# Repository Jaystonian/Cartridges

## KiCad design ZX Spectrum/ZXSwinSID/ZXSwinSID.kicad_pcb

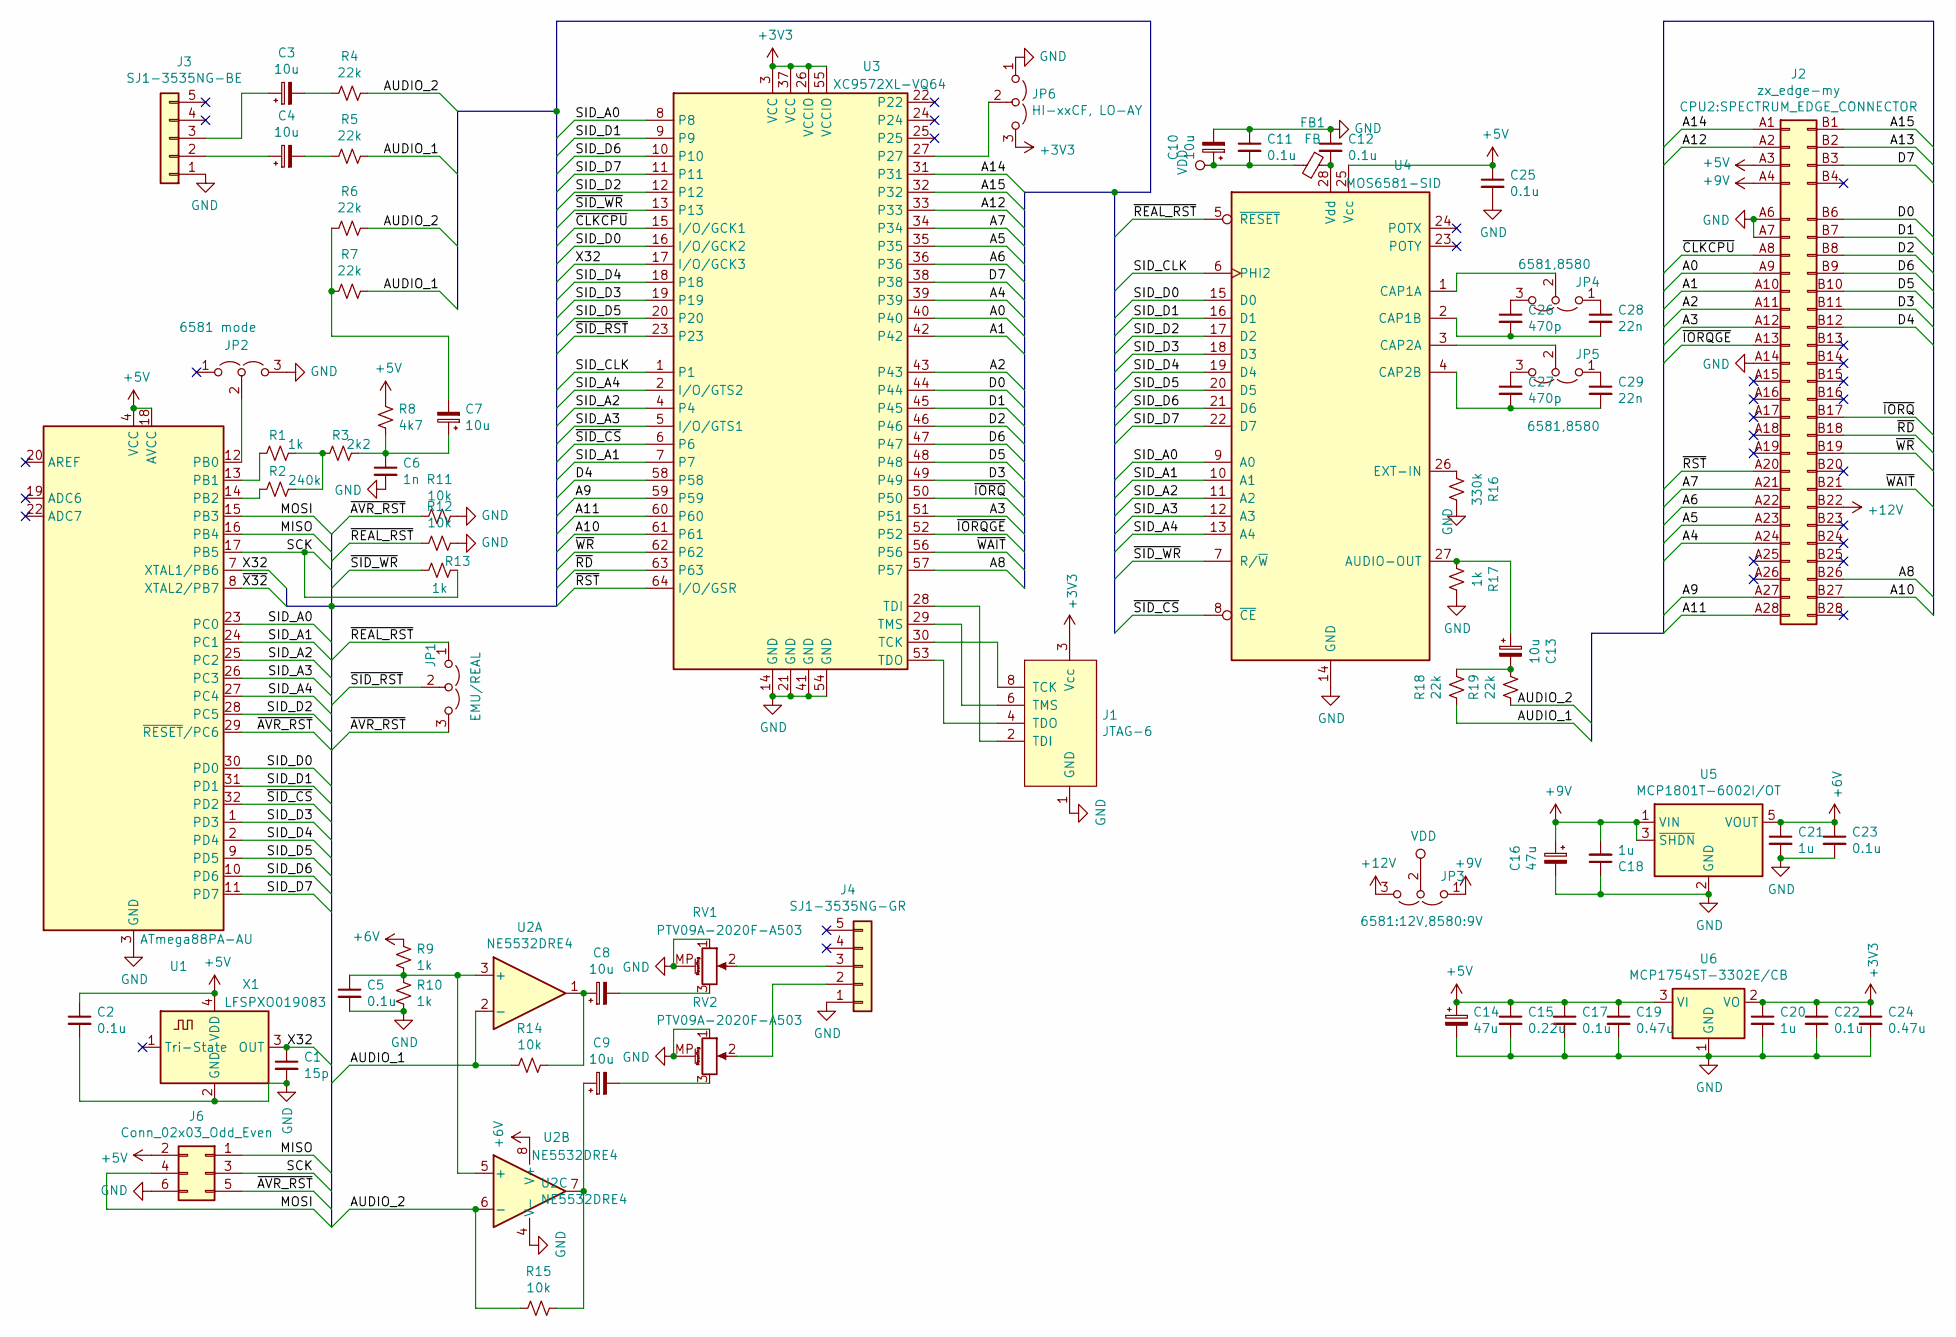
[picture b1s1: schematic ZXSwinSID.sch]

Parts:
C1: 15p; C_0805_2012Metric_Pad1.15x1.40mm_HandSolder
C2, C5, C11, C12, C17, C22, C23, C25: 0.1u; C_0805_2012Metric_Pad1.15x1.40mm_HandSolder
C3, C4, C7, C8, C9, C10, C13: 10u; CP_EIA-3216-18_Kemet-A_Pad1.58x1.35mm_HandSolder
C6: 1n; C_0805_2012Metric_Pad1.15x1.40mm_HandSolder
C14, C16: 47u; CP_EIA-6032-28_Kemet-C_Pad2.25x2.35mm_HandSolder
C15: 0.22u; C_0805_2012Metric_Pad1.15x1.40mm_HandSolder
C18, C20, C21: 1u; C_0805_2012Metric_Pad1.15x1.40mm_HandSolder
C19, C24: 0.47u; C_0805_2012Metric_Pad1.15x1.40mm_HandSolder
C26, C27: 470p; C_0805_2012Metric_Pad1.15x1.40mm_HandSolder
C28, C29: 22n; C_0805_2012Metric_Pad1.15x1.40mm_HandSolder
FB1: FB; R_0805_2012Metric_Pad1.15x1.40mm_HandSolder
J1: JTAG-6
J2: zx_edge-my; SPECTRUM_EDGE_CONNECTOR
J3: SJ1-3535NG-BE; Audio_SJ1-3535NG
J4: SJ1-3535NG-GR; Audio_SJ1-3535NG
J6: Conn_02x03_Odd_Even; PinHeader_1x06_P2.54mm_Vertical_SMD_Pin1Right
JP1: EMU/REAL; PinHeader_1x03_P2.54mm_Vertical
JP2: 6581 mode; PinHeader_1x03_P2.54mm_Vertical
JP3: 6581:12V,8580:9V; PinHeader_1x03_P2.54mm_Vertical
JP4, JP5: 6581,8580; PinHeader_1x03_P2.54mm_Vertical
JP6: HI-xxCF, LO-AY; PinHeader_1x03_P2.54mm_Vertical
R1, R9, R10, R13, R17: 1k; R_0805_2012Metric_Pad1.15x1.40mm_HandSolder
R2: 240k; R_0805_2012Metric_Pad1.15x1.40mm_HandSolder
R3: 2k2; R_0805_2012Metric_Pad1.15x1.40mm_HandSolder
R4, R5, R6, R7, R18, R19: 22k; R_0805_2012Metric_Pad1.15x1.40mm_HandSolder
R8: 4k7; R_0805_2012Metric_Pad1.15x1.40mm_HandSolder
R11, R12, R14, R15: 10k; R_0805_2012Metric_Pad1.15x1.40mm_HandSolder
R16: 330k; R_0805_2012Metric_Pad1.15x1.40mm_HandSolder
RV1, RV2: PTV09A-2020F-A503; Potentiometer_Bourns_PTV09A-2_Single_Horizontal
U1: ATmega88PA-AU; TQFP-32_7x7mm_P0.8mm
U2: NE5532DRE4; SOIC-8_3.9x4.9mm_P1.27mm
U3: XC9572XL-VQ64; TQFP-64_10x10mm_P0.5mm
U4: MOS6581-SID; DIP-28_W15.24mm_Socket
U5: MCP1801T-6002I/OT; SOT-23-5
U6: MCP1754ST-3302E/CB; SOT-23
X1: LFSPXO019083; Oscillator_SMD_IQD_IQXO70-4Pin_7.5x5.0mm_HandSoldering

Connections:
+3V3: C20.1, C22.1, C24.1, J1.3 (Vcc), JP6.3 (B), U3.3 (VCC), U3.26 (VCCIO), U3.37 (VCC), U3.55 (VCCIO), U6.2 (VO)
+5V: C2.1, C14.1, C15.1, C17.1, C19.1, C25.1, J2.A3 (Pin_a3), J6.2, R8.2, U1.4 (VCC), U1.6 (VCC), U1.18 (AVCC), U4.25 (Vcc), U6.3 (VI), X1.4 (VDD)
+6V: C21.1, C23.1, R9.1, U2.8 (V+), U5.5 (VOUT)
+9V: C16.1, C18.2, J2.A4 (Pin_a4), JP3.1 (A), U5.1 (VIN), U5.3 (~SHDN)
+12V: J2.B22 (Pin_b22), JP3.3 (B)
/A0: J2.A9 (Pin_a9), U3.40
/A1: J2.A10 (Pin_a10), U3.42
/A2: J2.A11 (Pin_a11), U3.43
/A3: J2.A12 (Pin_a12), U3.51
/A4: J2.A24 (Pin_a24), U3.39
/A5: J2.A23 (Pin_a23), U3.35
/A6: J2.A22 (Pin_a22), U3.36
/A7: J2.A21 (Pin_a21), U3.34
/A8: J2.B26 (Pin_b26), U3.57
/A9: J2.A27 (Pin_a27), U3.59
/A10: J2.B27 (Pin_b27), U3.61
/A11: J2.A28 (Pin_a28), U3.60
/A12: J2.A2 (Pin_a2), U3.33
/A13: J2.B2 (Pin_b2)
/A14: J2.A1 (Pin_a1), U3.31
/A15: J2.B1 (Pin_b1), U3.32
/AUDIO_1: R5.1, R7.1, R14.2, R18.2, U2.2 (-)
/AUDIO_2: R4.1, R6.1, R15.2, R19.2, U2.6 (-)
/D0: J2.B6 (Pin_b6), U3.44
/D1: J2.B7 (Pin_b7), U3.45
/D2: J2.B8 (Pin_b8), U3.46
/D3: J2.B11 (Pin_b11), U3.49
/D4: J2.B12 (Pin_b12), U3.58
/D5: J2.B10 (Pin_b10), U3.48
/D6: J2.B9 (Pin_b9), U3.47
/D7: J2.B3 (Pin_b3), U3.38
/MISO: J6.1, U1.16 (PB4)
/MOSI: J6.4, U1.15 (PB3)
/SCK: J6.3, R13.1, U1.17 (PB5)
/SID_A0: U1.23 (PC0), U3.8, U4.9 (A0)
/SID_A1: U1.24 (PC1), U3.7, U4.10 (A1)
/SID_A2: U1.25 (PC2), U3.4, U4.11 (A2)
/SID_A3: U1.26 (PC3), U3.5 (I/O/GTS1), U4.12 (A3)
/SID_A4: U1.27 (PC4), U3.2 (I/O/GTS2), U4.13 (A4)
/SID_CLK: U3.1, U4.6 (PHI2)
/SID_D0: U1.30 (PD0), U3.16 (I/O/GCK2), U4.15 (D0)
/SID_D1: U1.31 (PD1), U3.9, U4.16 (D1)
/SID_D2: U1.28 (PC5), U3.12, U4.17 (D2)
/SID_D3: U1.1 (PD3), U3.19, U4.18 (D3)
/SID_D4: U1.2 (PD4), U3.18, U4.19 (D4)
/SID_D5: U1.9 (PD5), U3.20, U4.20 (D5)
/SID_D6: U1.10 (PD6), U3.10, U4.21 (D6)
/SID_D7: U1.11 (PD7), U3.11, U4.22 (D7)
/X32: C1.1, U1.7 (XTAL1/PB6), U3.17 (I/O/GCK3), X1.3 (OUT)
/~AVR_RST: J6.5, JP1.3 (B), R11.2, U1.29 (~RESET~/PC6)
/~CLKCPU: J2.A8 (Pin_a8), U3.15 (I/O/GCK1)
/~IORQ: J2.B17 (Pin_b17), U3.50
/~IORQGE: J2.A13 (Pin_a13), U3.52
/~RD: J2.B18 (Pin_b18), U3.63
/~REAL_RST: JP1.1 (A), R12.2, U4.5 (~RESET~)
/~RST: J2.A20 (Pin_a20), U3.64 (I/O/GSR)
/~SID_CS: U1.32 (PD2), U3.6, U4.8 (~CE~)
/~SID_RST: JP1.2 (C), U3.23
/~SID_WR: R13.2, U3.13, U4.7 (R/~W~)
/~WAIT: J2.B21 (Pin_b21), U3.56
/~WR: J2.B19 (Pin_b19), U3.62
/~X32: U1.8 (XTAL2/PB7)
GND: C1.2, C2.2, C5.2, C6.2, C10.2, C11.1, C12.1, C14.2, C15.2, C16.2, C17.2, C18.1, C19.2, C20.2, C21.2, C22.2, C23.2, C24.2, C25.2, J1.1 (GND), J2.A6 (Pin_a6), J2.A7 (Pin_a7), J2.A14 (Pin_a14), J3.1, J4.1, J6.6, JP2.3 (B), JP6.1 (A), R10.2, R11.1, R12.1, R16.1, R17.1, RV1.1, RV1.MP (MountPin), RV2.1, RV2.MP (MountPin), U1.3 (GND), U1.5 (GND), U1.21 (GND), U2.4 (V-), U3.14 (GND), U3.21 (GND), U3.41 (GND), U3.54 (GND), U4.14 (GND), U5.2 (GND), U6.1 (GND), X1.2 (GND)
unnamed: C3.1, J3.3
unnamed: C3.2, R4.2
unnamed: C4.1, J3.2
unnamed: C4.2, R5.2
unnamed: C5.1, R9.2, R10.1, U2.3 (+), U2.5 (+)
unnamed: C6.1, C7.1, R3.1, R8.1
unnamed: C7.2, R6.2, R7.2
unnamed: C8.1, R14.1, U2.1
unnamed: C8.2, RV1.3
unnamed: C9.1, R15.1, U2.7
unnamed: C9.2, RV2.3
unnamed: C12.2, FB1.1, U4.28 (Vdd)
unnamed: C13.1, R17.2, U4.27 (AUDIO-OUT)
unnamed: C13.2, R18.1, R19.1
unnamed: C26.1, JP4.3 (B)
unnamed: C26.2, C28.2, U4.2 (CAP1B)
unnamed: C27.1, JP5.3 (B)
unnamed: C27.2, C29.2, U4.4 (CAP2B)
unnamed: C28.1, JP4.1 (A)
unnamed: C29.1, JP5.1 (A)
unnamed: J1.2 (TDI), U3.28 (TDI)
unnamed: J1.4 (TDO), U3.53 (TDO)
unnamed: J1.6 (TMS), U3.29 (TMS)
unnamed: J1.8 (TCK), U3.30 (TCK)
unnamed: J4.2, RV2.2
unnamed: J4.3, RV1.2
unnamed: JP2.2 (C), U1.12 (PB0)
unnamed: JP4.2 (C), U4.1 (CAP1A)
unnamed: JP5.2 (C), U4.3 (CAP2A)
unnamed: JP6.2 (C), U3.27
unnamed: R1.1, R2.1, R3.2
unnamed: R1.2, U1.13 (PB1)
unnamed: R2.2, U1.14 (PB2)
unnamed: R16.2, U4.26 (EXT-IN)
VDD: C10.1, C11.2, FB1.2, JP3.2 (C)

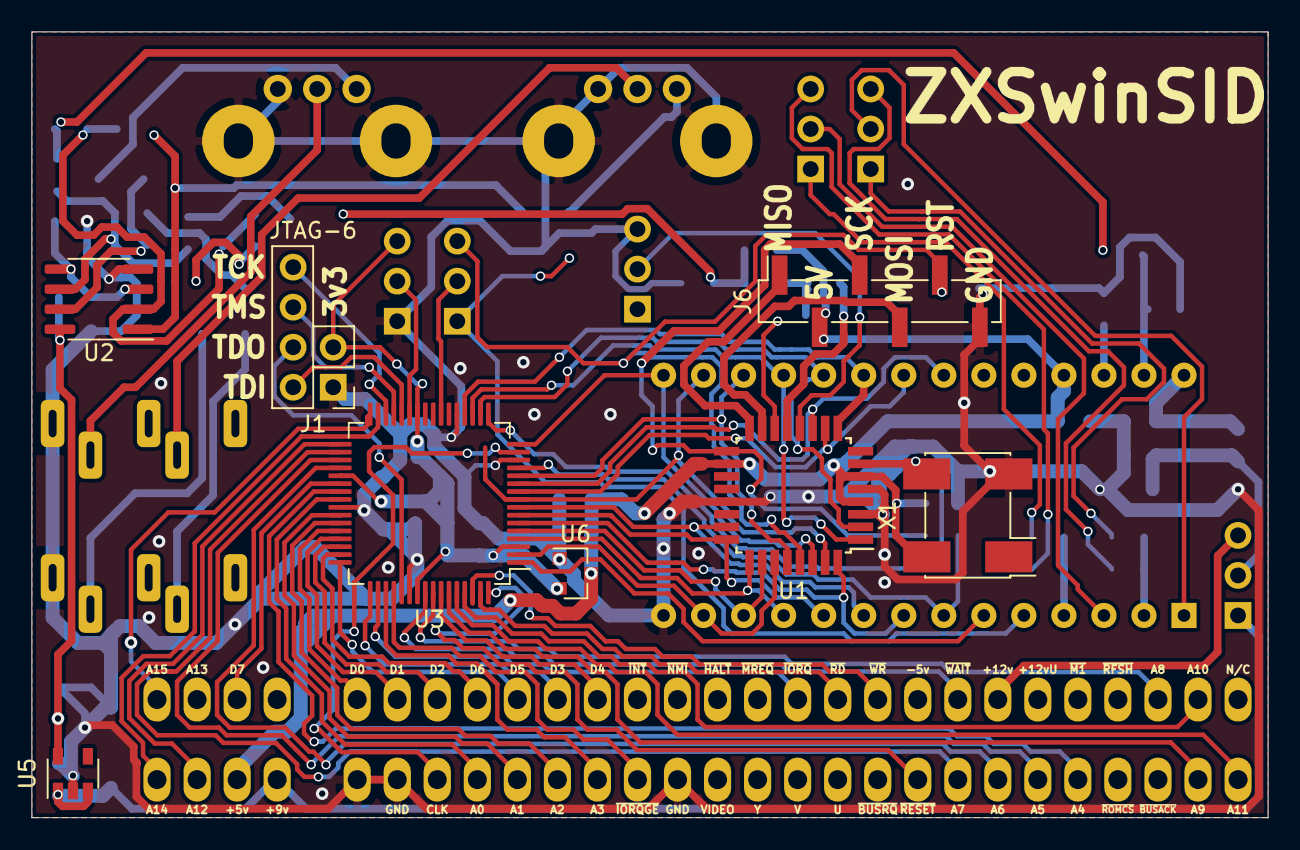
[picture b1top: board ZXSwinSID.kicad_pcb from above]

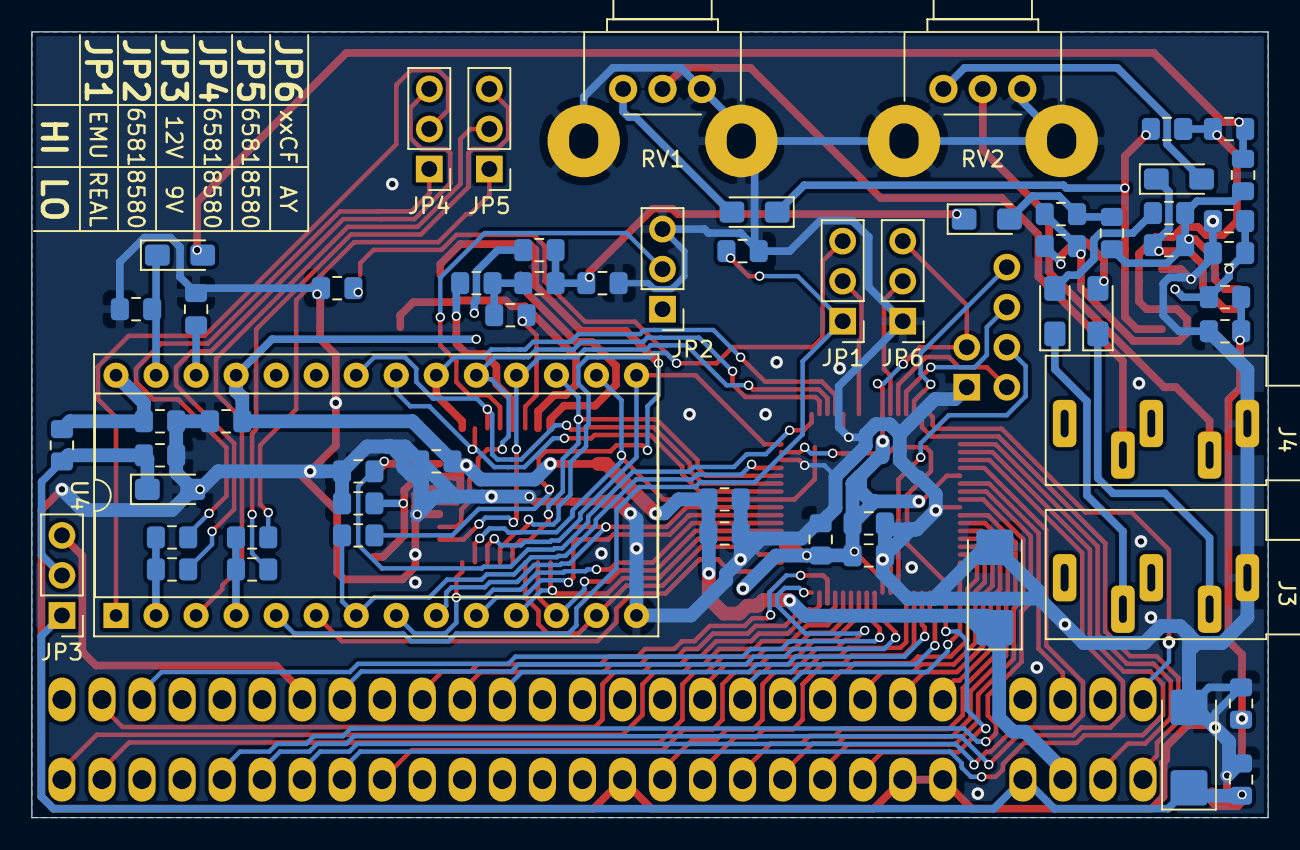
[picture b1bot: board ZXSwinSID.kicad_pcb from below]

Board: 2 copper layers, 78.4 x 49.8 mm, 69 parts (60 on the bottom side), 96 nets.

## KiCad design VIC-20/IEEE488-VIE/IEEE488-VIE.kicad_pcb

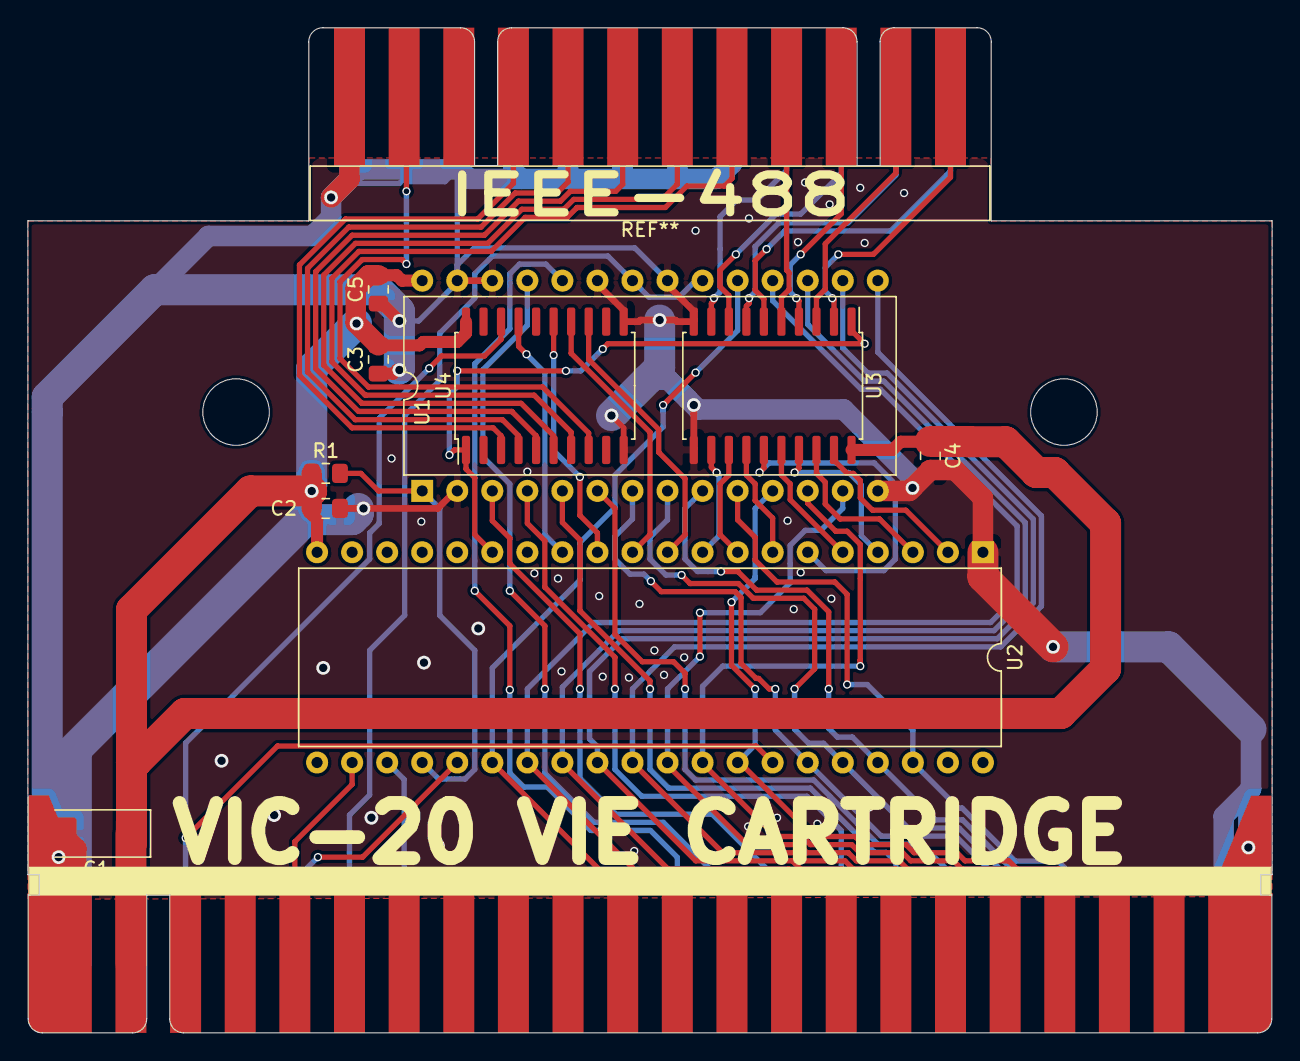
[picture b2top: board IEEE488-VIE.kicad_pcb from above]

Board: 2 copper layers, 90.2 x 72.8 mm, 12 parts (0 on the bottom side), 53 nets.

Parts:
C1: 22u; CP_EIA-6032-28_Kemet-C_Pad2.25x2.35mm_HandSolder
C2, C3, C4, C5: 0.1u; C_0805_2012Metric_Pad1.15x1.40mm_HandSolder
MEDGE1: IEEE-488; IEEE-488_CARD_EDGE
R1: 3k3; R_0805_2012Metric_Pad1.15x1.40mm_HandSolder
U1: 27C256; DIP-28_W15.24mm
U2: W65C22VIA-40DIP; DIP-40_W15.24mm
U3: SN75160BDW; SOIC-20W_7.5x12.8mm_P1.27mm
U4: SN75161BDW; SOIC-20W_7.5x12.8mm_P1.27mm
X1: VIC20_EXPANSION_PORT; VIC20_EXPANSION_CARD_2

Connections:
+5V: C1.1, C2.1, C3.1, C4.1, C5.1, R1.1, U1.28, U2.20, U3.20, U4.20, X1.21
/ATN: MEDGE1.11, U4.8
/CA0: U1.10, U2.38, X1.B
/CA1: U1.9, U2.37, X1.C
/CA2: U1.8, U2.36, X1.D
/CA3: U1.7, U2.35, X1.E
/CA4: U1.6, X1.F
/CA5: U1.5, X1.H
/CA6: U1.4, X1.J
/CA7: U1.3, X1.K
/CA8: U1.25, X1.L
/CA9: U1.24, X1.M
/CD0: U1.11, U2.33, X1.2
/CD1: U1.12, U2.32, X1.3
/CD2: U1.13, U2.31, X1.4
/CD3: U1.15, U2.30, X1.5
/CD4: U1.16, U2.29, X1.6
/CD5: U1.17, U2.28, X1.7
/CD6: U1.18, U2.27, X1.8
/CD7: U1.19, U2.26, X1.9
/CR~W: U2.22, X1.18
/DAV: MEDGE1.6, U4.6
/ED0: MEDGE1.1, U3.2
/ED1: MEDGE1.2, U3.3
/ED2: MEDGE1.3, U3.4
/ED3: MEDGE1.4, U3.5
/ED4: MEDGE1.13A, U3.6
/ED5: MEDGE1.14B, U3.7
/ED6: MEDGE1.15C, U3.8
/ED7: MEDGE1.16D, U3.9
/EOI: MEDGE1.5, U4.7
/IFC: MEDGE1.9, U4.3
/NDAC: MEDGE1.8, U4.4
/NRFD: MEDGE1.7, U4.5
/PA0: U2.2, U3.19
/PA1: U2.3, U3.18
/PA2: U2.4, U3.17
/PA3: U2.5, U3.16
/PA4: U2.6, U3.15
/PA5: U2.7, U3.14
/PA6: U2.8, U3.13
/PA7: U2.9, U3.12
/PULLHI: R1.2, U1.1, U2.24
/SPhi2: U2.25, X1.V
/TATN: U2.10, U4.13
/TDAV: U2.12, U4.15
/TE: U2.15, U3.1, U4.1
/TEOI: U2.11, U4.14
/TNDAC: U2.13, U4.17
/~IO2: U2.23, X1.T
/~IO3: U1.20, U1.22, X1.U
/~RESET: U2.34, U4.18, X1.X
GND: C1.2, C2.2, C3.2, C4.2, C5.2, MEDGE1.12, MEDGE1.17E, MEDGE1.18F, MEDGE1.19H, MEDGE1.20J, MEDGE1.21K, MEDGE1.22L, MEDGE1.23M, MEDGE1.24N, U1.2, U1.14, U1.21, U1.23, U1.26, U1.27, U2.1, U3.10, U3.11, U4.10, U4.11, X1.1, X1.22, X1.A, X1.Z

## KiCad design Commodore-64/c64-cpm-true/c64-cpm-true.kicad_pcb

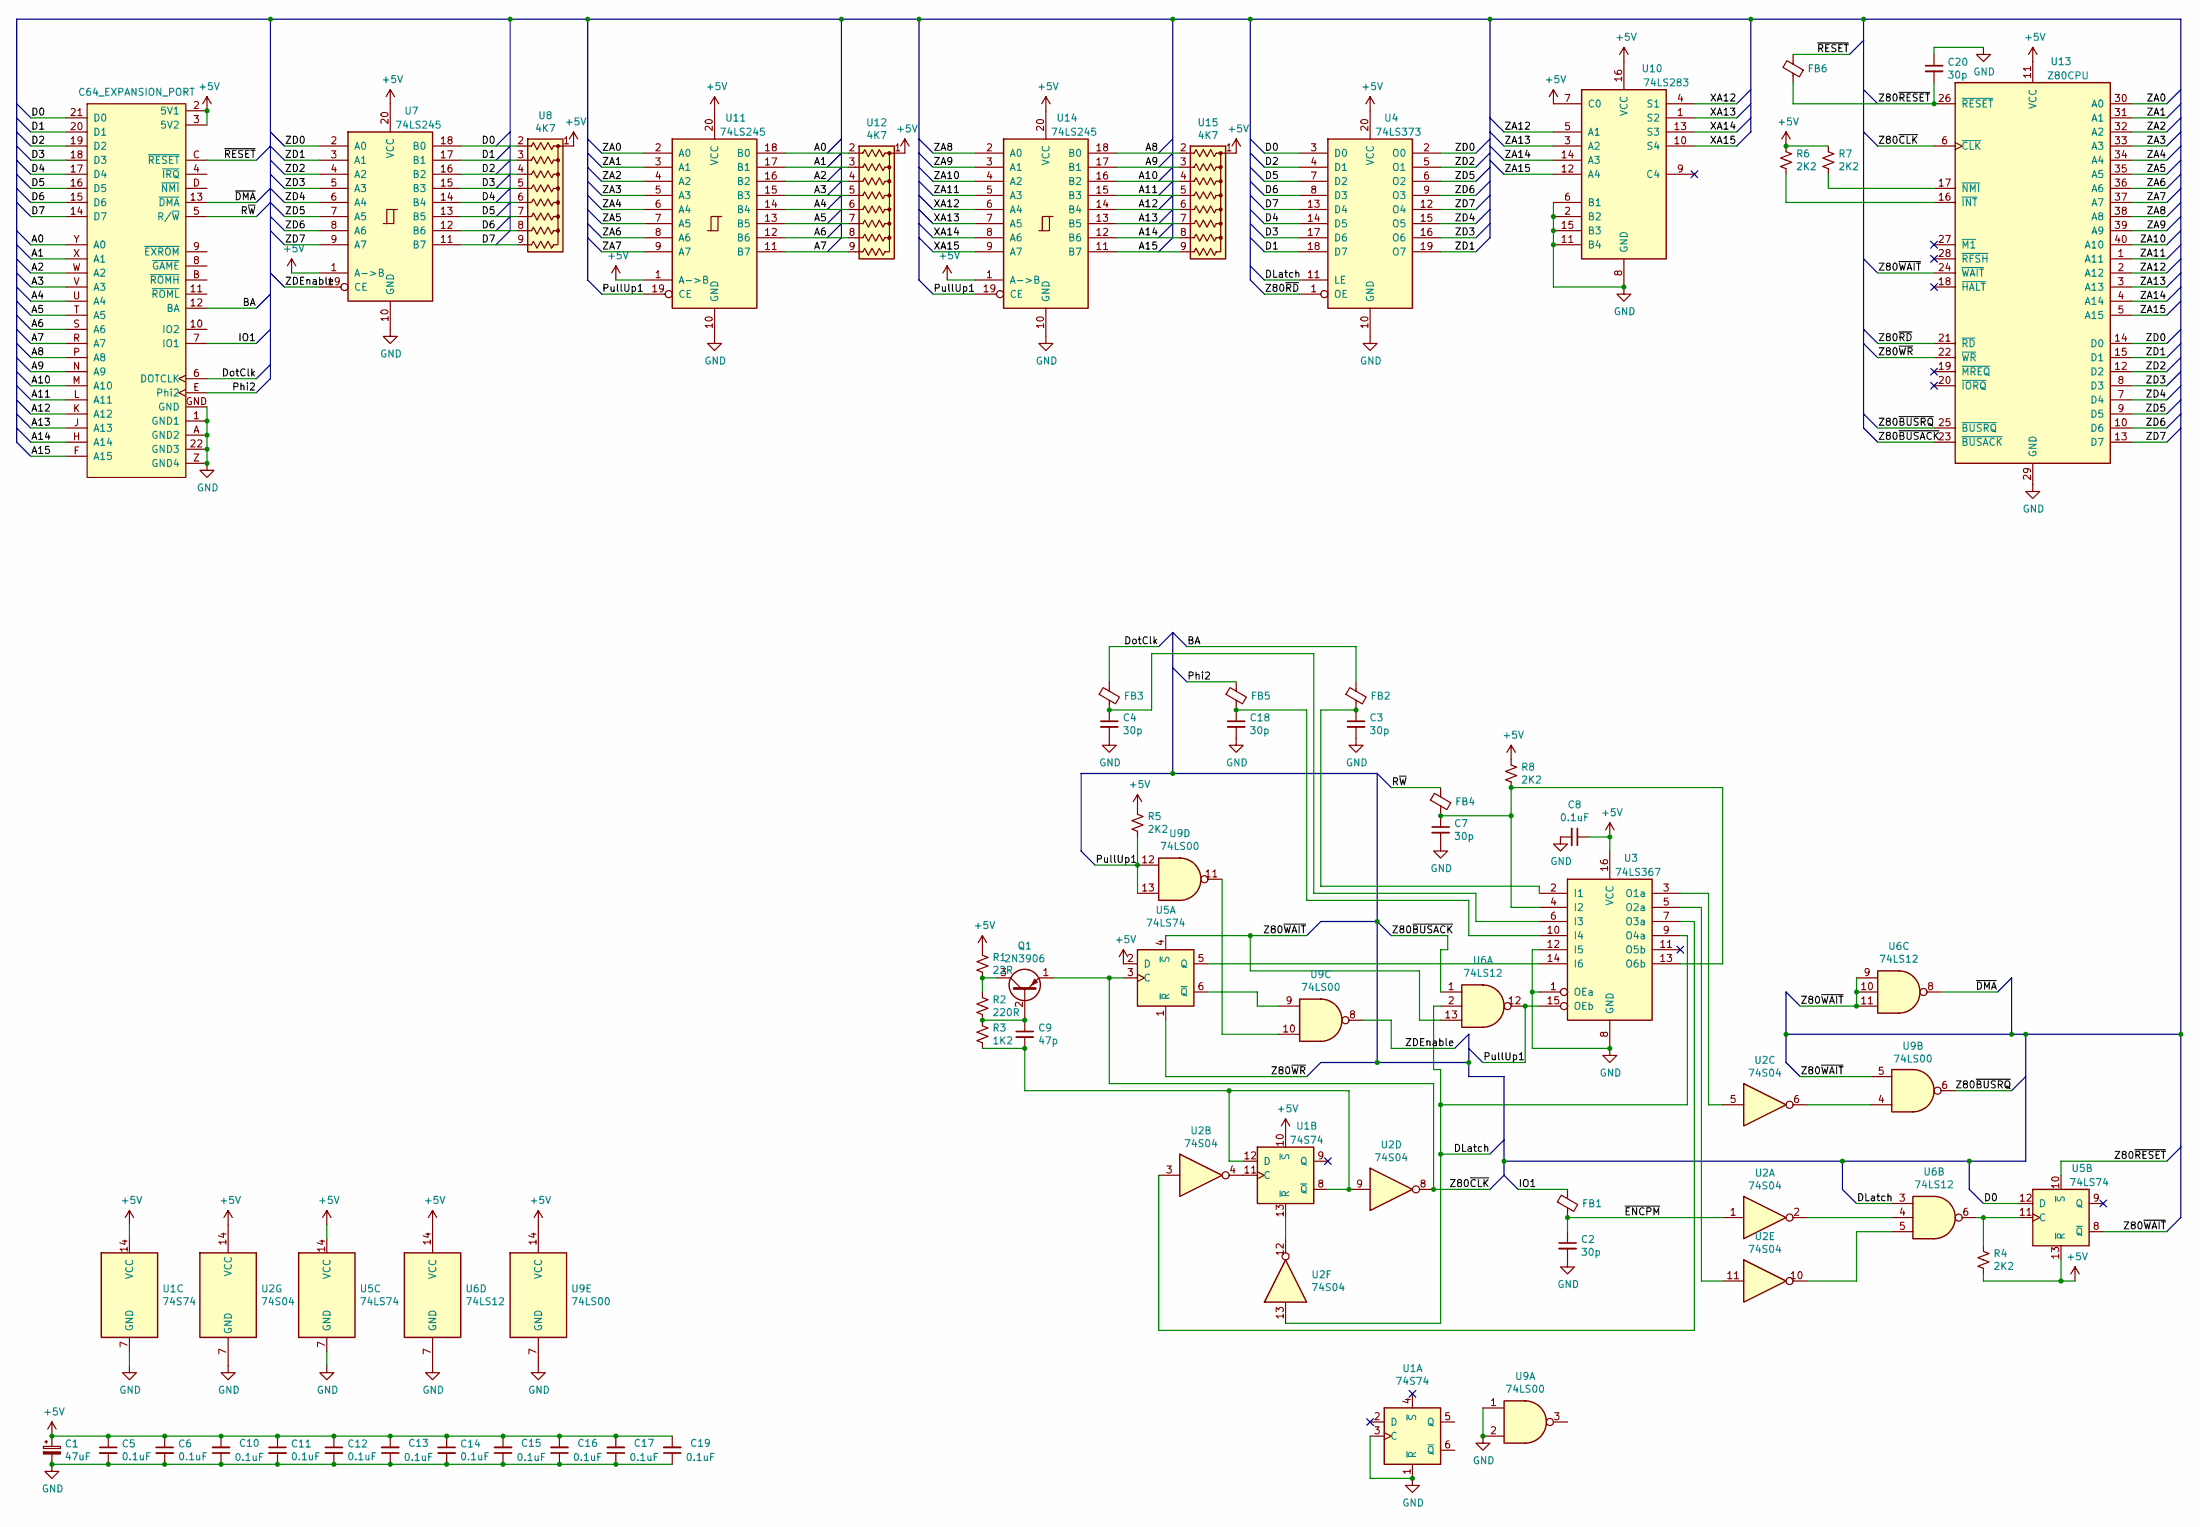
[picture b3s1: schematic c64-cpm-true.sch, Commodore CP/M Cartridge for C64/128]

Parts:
C1: 47uF; CP_Axial_L18.0mm_D8.0mm_P25.00mm_Horizontal
C2, C3, C4, C7, C18, C20: 30p; R_Axial_DIN0204_L3.6mm_D1.6mm_P12.7mm_Horizontal
C5, C6, C8, C10, C11, C12, C13, C14, C15, C16, C17, C19: 0.1uF; C_Disc_D4.3mm_W1.9mm_P5.00mm
C9: 47p; R_Axial_DIN0204_L3.6mm_D1.6mm_P12.7mm_Horizontal
FB1, FB2, FB3, FB4, FB5, FB6: 2508052027Z0; R_Axial_DIN0204_L3.6mm_D1.6mm_P12.7mm_Horizontal
Q1: 2N3906; TO-92L_Inline_Wide
R1: 22R; R_Axial_DIN0204_L3.6mm_D1.6mm_P12.7mm_Horizontal
R2: 220R; R_Axial_DIN0204_L3.6mm_D1.6mm_P12.7mm_Horizontal
R3: 1K2; R_Axial_DIN0204_L3.6mm_D1.6mm_P12.7mm_Horizontal
R4, R5, R6, R7, R8: 2K2; R_Axial_DIN0204_L3.6mm_D1.6mm_P12.7mm_Horizontal
U1: 74S74; DIP-14_W7.62mm
U2: 74S04; DIP-14_W7.62mm
U3: 74LS367; DIP-16_W7.62mm
U4: 74LS373; DIP-20_W7.62mm
U5: 74LS74; DIP-14_W7.62mm
U6: 74LS12; DIP-14_W7.62mm
U7, U11, U14: 74LS245; DIP-20_W7.62mm
U8, U12, U15: 4K7; R_Array_SIP9
U9: 74LS00; DIP-14_W7.62mm
U10: 74LS283; DIP-16_W7.62mm
U13: Z80CPU; DIP-40_W15.24mm
X1: C64_EXPANSION_PORT; C64_EXPANSION_CARD_129x105mm

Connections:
+5V: C1.1, C5.1, C6.1, C8.1, C10.2, C11.1, C12.1, C13.2, C14.1, C15.2, C16.2, C17.2, C19.2, R1.1, R4.2, R5.1, R6.1, R7.1, R8.1, U1.10 (~S), U1.14 (VCC), U2.14 (VCC), U3.16 (VCC), U4.20 (VCC), U5.2 (D), U5.13 (~R), U5.14 (VCC), U6.14 (VCC), U7.1 (A->B), U7.20 (VCC), U8.1 (common), U9.14 (VCC), U10.7 (C0), U10.16 (VCC), U11.1 (A->B), U11.20 (VCC), U12.1 (common), U13.11 (VCC), U14.1 (A->B), U14.20 (VCC), U15.1 (common), X1.2 (5V1), X1.3 (5V2)
/A0: U11.18 (B0), U12.2 (R1), X1.Y (A0)
/A1: U11.17 (B1), U12.3 (R2), X1.X (A1)
/A2: U11.16 (B2), U12.4 (R3), X1.W (A2)
/A3: U11.15 (B3), U12.5 (R4), X1.V (A3)
/A4: U11.14 (B4), U12.6 (R5), X1.U (A4)
/A5: U11.13 (B5), U12.7 (R6), X1.T (A5)
/A6: U11.12 (B6), U12.8 (R7), X1.S (A6)
/A7: U11.11 (B7), U12.9 (R8), X1.R (A7)
/A8: U14.18 (B0), U15.2 (R1), X1.P (A8)
/A9: U14.17 (B1), U15.3 (R2), X1.N (A9)
/A10: U14.16 (B2), U15.4 (R3), X1.M (A10)
/A11: U14.15 (B3), U15.5 (R4), X1.L (A11)
/A12: U14.14 (B4), U15.6 (R5), X1.K (A12)
/A13: U14.13 (B5), U15.7 (R6), X1.J (A13)
/A14: U14.12 (B6), U15.8 (R7), X1.H (A14)
/A15: U14.11 (B7), U15.9 (R8), X1.F (A15)
/BA: FB2.1, X1.12 (BA)
/D0: U4.3 (D0), U5.12 (D), U7.18 (B0), U8.2 (R1), X1.21 (D0)
/D1: U4.18 (D7), U7.17 (B1), U8.3 (R2), X1.20 (D1)
/D2: U4.4 (D1), U7.16 (B2), U8.4 (R3), X1.19 (D2)
/D3: U4.17 (D6), U7.15 (B3), U8.5 (R4), X1.18 (D3)
/D4: U4.14 (D5), U7.14 (B4), U8.6 (R5), X1.17 (D4)
/D5: U4.7 (D2), U7.13 (B5), U8.7 (R6), X1.16 (D5)
/D6: U4.8 (D3), U7.12 (B6), U8.8 (R7), X1.15 (D6)
/D7: U4.13 (D4), U7.11 (B7), U8.9 (R8), X1.14 (D7)
/DLatch: U2.13, U3.9 (O4a), U4.11 (LE), U6.2, U6.3
/DotClk: FB3.1, X1.6 (DOTCLK)
/IO1: FB1.1, X1.7 (IO1)
/Phi2: FB5.1, X1.E (Phi2)
/PullUp1: R5.2, U3.15 (OEb), U6.12, U9.12, U9.13, U11.19 (CE), U14.19 (CE)
/R~W: FB4.1, X1.5 (R/~W~)
/XA12: U10.4 (S1), U14.6 (A4)
/XA13: U10.1 (S2), U14.7 (A5)
/XA14: U10.13 (S3), U14.8 (A6)
/XA15: U10.10 (S4), U14.9 (A7)
/Z80~BUSACK: U6.1, U13.23 (~BUSACK~)
/Z80~BUSRQ: U9.6, U13.25 (~BUSRQ~)
/Z80~CLK: Q1.1 (E), U2.8, U5.3 (C), U13.6 (~CLK~)
/Z80~RD: U4.1 (OE), U13.21 (~RD~)
/Z80~RESET: C20.2, FB6.1, U5.10 (~S), U13.26 (~RESET~)
/Z80~WAIT: U5.4 (~S), U5.8 (~Q), U6.9, U6.10, U6.11, U6.13, U9.5, U13.24 (~WAIT~)
/Z80~WR: U5.1 (~R), U13.22 (~WR~)
/ZA0: U11.2 (A0), U13.30 (A0)
/ZA1: U11.3 (A1), U13.31 (A1)
/ZA2: U11.4 (A2), U13.32 (A2)
/ZA3: U11.5 (A3), U13.33 (A3)
/ZA4: U11.6 (A4), U13.34 (A4)
/ZA5: U11.7 (A5), U13.35 (A5)
/ZA6: U11.8 (A6), U13.36 (A6)
/ZA7: U11.9 (A7), U13.37 (A7)
/ZA8: U13.38 (A8), U14.2 (A0)
/ZA9: U13.39 (A9), U14.3 (A1)
/ZA10: U13.40 (A10), U14.4 (A2)
/ZA11: U13.1 (A11), U14.5 (A3)
/ZA12: U10.5 (A1), U13.2 (A12)
/ZA13: U10.3 (A2), U13.3 (A13)
/ZA14: U10.14 (A3), U13.4 (A14)
/ZA15: U10.12 (A4), U13.5 (A15)
/ZD0: U4.2 (O0), U7.2 (A0), U13.14 (D0)
/ZD1: U4.19 (O7), U7.3 (A1), U13.15 (D1)
/ZD2: U4.5 (O1), U7.4 (A2), U13.12 (D2)
/ZD3: U4.16 (O6), U7.5 (A3), U13.8 (D3)
/ZD4: U4.15 (O5), U7.6 (A4), U13.7 (D4)
/ZD5: U4.6 (O2), U7.7 (A5), U13.9 (D5)
/ZD6: U4.9 (O3), U7.8 (A6), U13.10 (D6)
/ZD7: U4.12 (O4), U7.9 (A7), U13.13 (D7)
/ZDEnable: U7.19 (CE), U9.8
/~DMA: U6.8, X1.13 (~DMA~)
/~RESET: FB6.2, X1.C (~RESET~)
GND: C1.2, C2.2, C3.2, C4.2, C5.2, C6.2, C7.2, C8.2, C10.1, C11.2, C12.2, C13.1, C14.2, C15.1, C16.1, C17.1, C18.2, C19.1, C20.1, U1.1 (~R), U1.3 (C), U1.7 (GND), U2.7 (GND), U3.1 (OEa), U3.8 (GND), U3.12 (I5), U4.10 (GND), U5.7 (GND), U6.7 (GND), U7.10 (GND), U9.1, U9.2, U9.7 (GND), U10.2 (B2), U10.6 (B1), U10.8 (GND), U10.11 (B4), U10.15 (B3), U11.10 (GND), U13.29 (GND), U14.10 (GND), X1.1 (GND1), X1.22 (GND3), X1.A (GND2), X1.GND, X1.Z (GND4)
unnamed: C2.1, FB1.2, U2.1
unnamed: C3.1, FB2.2, U3.2 (I1)
unnamed: C4.1, FB3.2, U3.6 (I3)
unnamed: C7.1, FB4.2, R8.2, U3.4 (I2), U3.13 (O6b)
unnamed: C9.1, Q1.2 (B), R2.2, R3.1
unnamed: C9.2, R3.2, U1.8 (~Q), U1.12 (D), U2.9
unnamed: C18.1, FB5.2, U3.10 (I4)
unnamed: Q1.3 (C), R1.2, R2.1
unnamed: R4.1, U5.11 (C), U6.6
unnamed: R6.2, U13.16 (~INT~)
unnamed: R7.2, U13.17 (~NMI~)
unnamed: U1.11 (C), U2.4
unnamed: U1.13 (~R), U2.12
unnamed: U2.2, U6.4
unnamed: U2.3, U3.7 (O3a)
unnamed: U2.5, U3.3 (O1a)
unnamed: U2.6, U9.4
unnamed: U2.10, U6.5
unnamed: U2.11, U3.5 (O2a)
unnamed: U3.14 (I6), U5.5 (Q)
unnamed: U5.6 (~Q), U9.9
unnamed: U9.10, U9.11

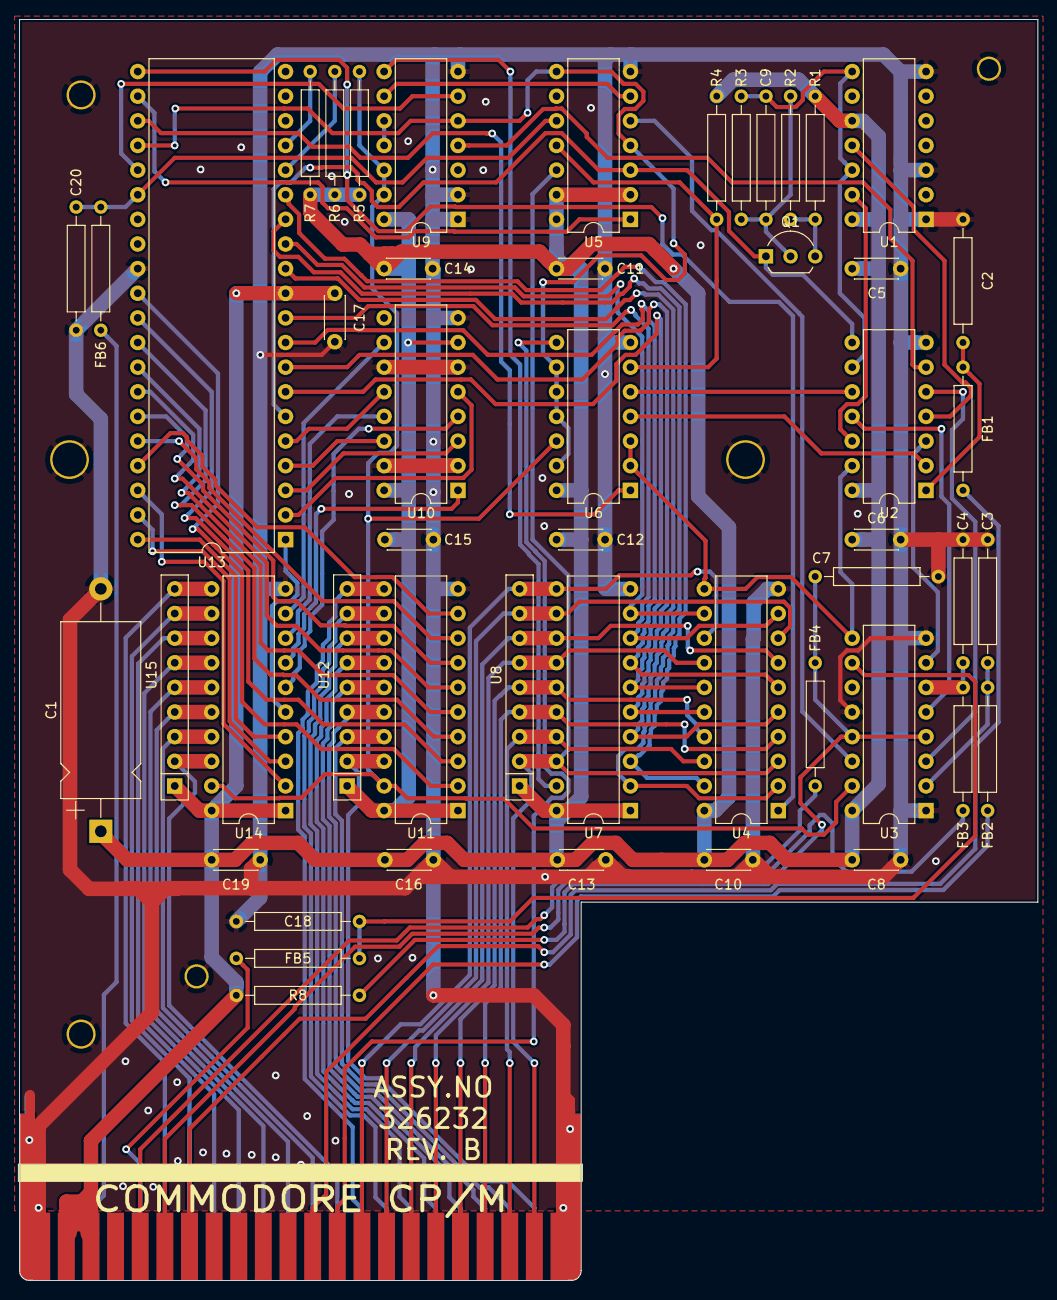
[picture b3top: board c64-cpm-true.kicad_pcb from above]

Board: 2 copper layers, 105.0 x 130.0 mm, 51 parts (0 on the bottom side), 93 nets.

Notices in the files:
Commodore-64/MONster64/code/source-kff/firmware/stm32f4xx/c64_interface.c:
Copyright (c) 2019-2020 Kim Jørgensen
